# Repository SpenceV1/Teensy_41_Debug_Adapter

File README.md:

# Teensy_41_Debug_Adapter
See [Teensy_41_Debug_PCB](https://github.com/SpenceV1/Teensy_41_Debug_PCB)

[OSHPARK](https://oshpark.com/shared_projects/izZXmeEX)

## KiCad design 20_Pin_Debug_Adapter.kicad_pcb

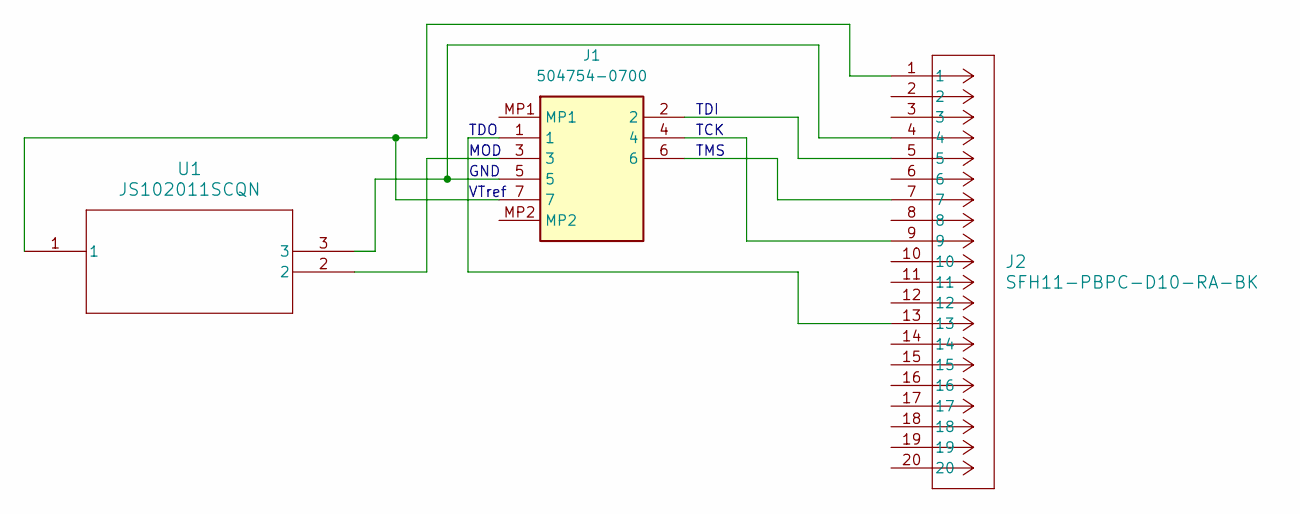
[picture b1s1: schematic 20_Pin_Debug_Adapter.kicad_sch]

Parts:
J1: 504754-0700; 5047540700; Mouser Part Number 538-504754-0700
J2: SFH11-PBPC-D10-RA-BK; CONN20_D10-RA-BK_SUL
U1: JS102011SCQN; SWITCH_1SCQN

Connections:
unnamed: J1.1, J2.13
unnamed: J1.2, J2.5
unnamed: J1.3, U1.2
unnamed: J1.4, J2.9
unnamed: J1.5, J2.4, U1.3
unnamed: J1.6, J2.7
unnamed: J1.7, J2.1, U1.1

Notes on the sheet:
TDI
TMS
TDO
TCK
GND
VTref
MOD

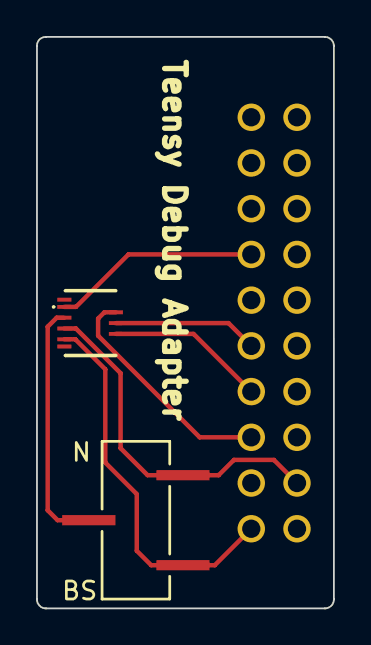
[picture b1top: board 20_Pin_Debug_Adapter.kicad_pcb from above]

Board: 2 copper layers, 16.5 x 31.8 mm, 3 parts (0 on the bottom side), 7 nets.

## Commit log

2023-07-16 Added 0.25mm to FPC Connector Pads
    Lengthened FPC connector pads outward by 0.25mm for easier soldering
2023-08-22 Update README.md
    Added Link to Teensy_41_Debug_PCB
2023-08-25 Update README.md
    Added OSHPARK link
